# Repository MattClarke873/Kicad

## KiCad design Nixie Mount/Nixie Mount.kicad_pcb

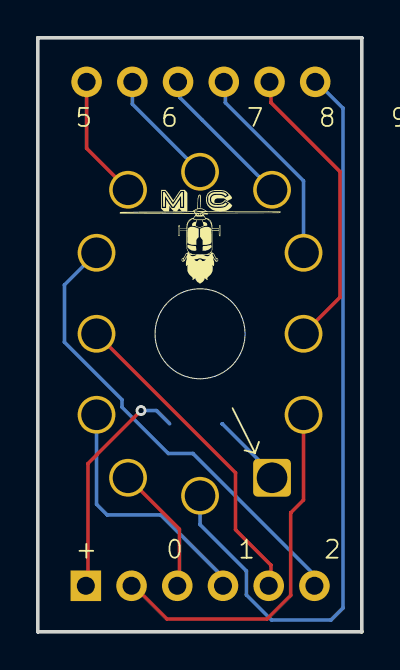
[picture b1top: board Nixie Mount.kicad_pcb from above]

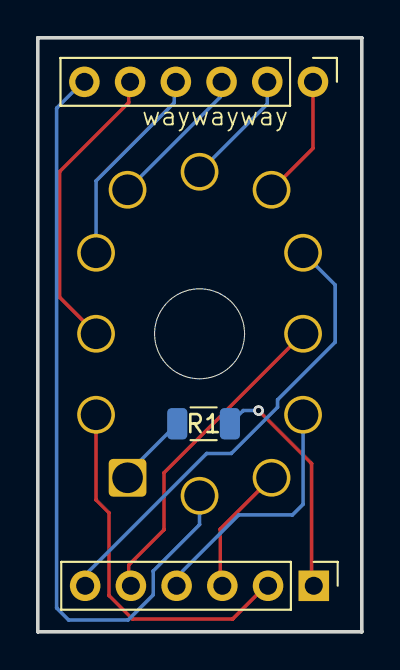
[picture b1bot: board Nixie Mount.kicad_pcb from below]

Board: 2 copper layers, 18.0 x 33.0 mm, 4 parts (3 on the bottom side), 13 nets.

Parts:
J1, J2: TSW-106-07-G-S-LL; PinHeader_1x06_P2.54mm_Vertical
NT1: IN-12
R1: R; R_1206_3216Metric

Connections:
unnamed: J2.1, NT1.7
unnamed: J1.6, NT1.8
unnamed: J1.5, NT1.9
unnamed: J1.4, NT1.10
unnamed: J1.3, NT1.11
unnamed: J2.6, NT1.12
unnamed: J1.1, R1.1
unnamed: J1.2, NT1.2
unnamed: J2.5, NT1.3
unnamed: J2.4, NT1.4
unnamed: J2.3, NT1.5
unnamed: J2.2, NT1.6
unnamed: NT1.1, R1.2

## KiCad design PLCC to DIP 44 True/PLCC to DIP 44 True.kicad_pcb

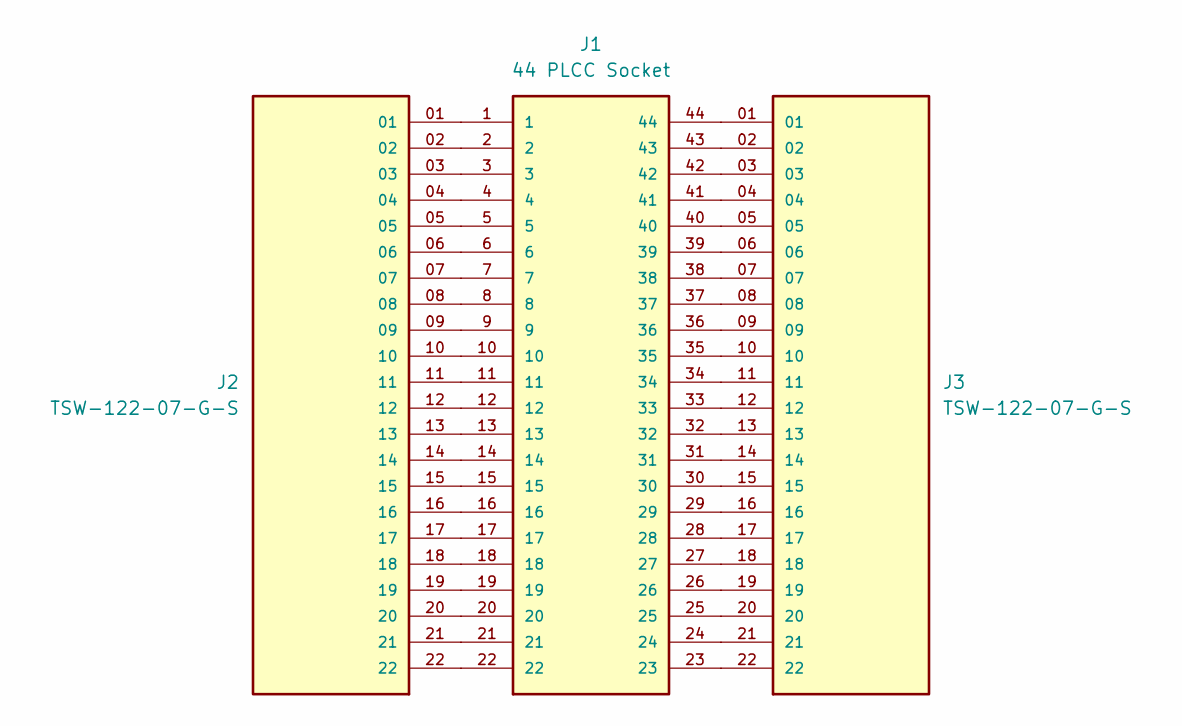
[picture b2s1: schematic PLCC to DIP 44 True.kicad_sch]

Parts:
J1: 44 PLCC Socket; AMPHENOL_54020-44030LF; PARTREV K
J2, J3: TSW-122-07-G-S; SAMTEC_TSW-122-07-G-S; PARTREV R

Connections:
unnamed: J1.1, J2.01
unnamed: J1.2, J2.02
unnamed: J1.3, J2.03
unnamed: J1.4, J2.04
unnamed: J1.5, J2.05
unnamed: J1.6, J2.06
unnamed: J1.7, J2.07
unnamed: J1.8, J2.08
unnamed: J1.9, J2.09
unnamed: J1.10, J2.10
unnamed: J1.11, J2.11
unnamed: J1.12, J2.12
unnamed: J1.13, J2.13
unnamed: J1.14, J2.14
unnamed: J1.15, J2.15
unnamed: J1.16, J2.16
unnamed: J1.17, J2.17
unnamed: J1.18, J2.18
unnamed: J1.19, J2.19
unnamed: J1.20, J2.20
unnamed: J1.21, J2.21
unnamed: J1.22, J2.22
unnamed: J1.23, J3.22
unnamed: J1.24, J3.21
unnamed: J1.25, J3.20
unnamed: J1.26, J3.19
unnamed: J1.27, J3.18
unnamed: J1.28, J3.17
unnamed: J1.29, J3.16
unnamed: J1.30, J3.15
unnamed: J1.31, J3.14
unnamed: J1.32, J3.13
unnamed: J1.33, J3.12
unnamed: J1.34, J3.11
unnamed: J1.35, J3.10
unnamed: J1.36, J3.09
unnamed: J1.37, J3.08
unnamed: J1.38, J3.07
unnamed: J1.39, J3.06
unnamed: J1.40, J3.05
unnamed: J1.41, J3.04
unnamed: J1.42, J3.03
unnamed: J1.43, J3.02
unnamed: J1.44, J3.01

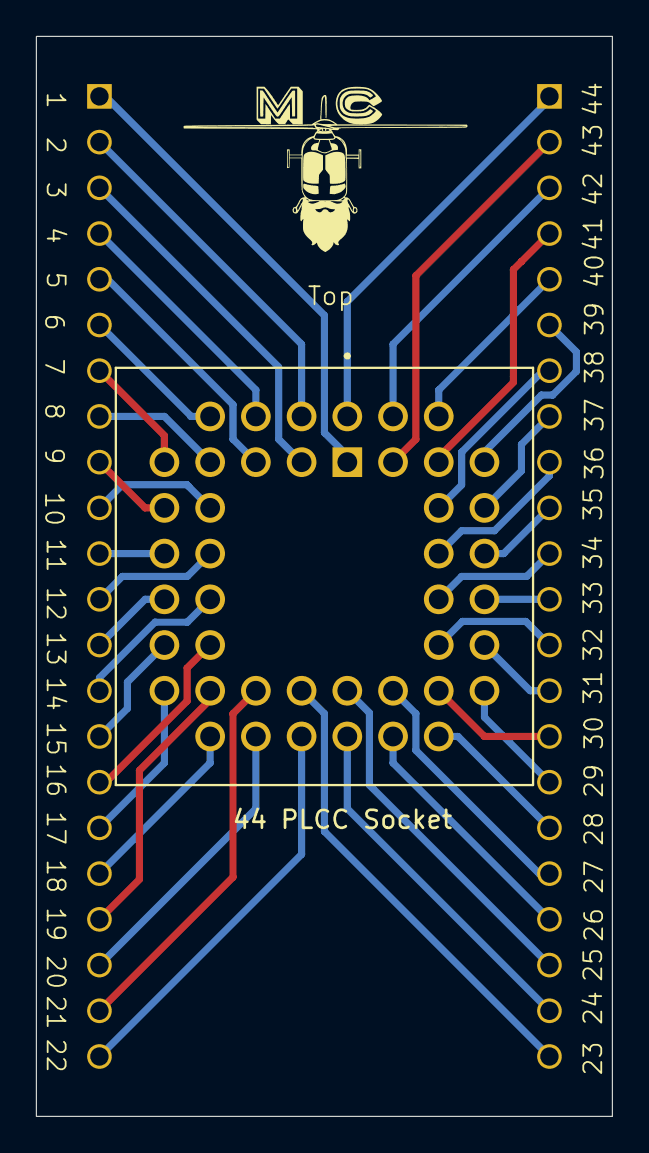
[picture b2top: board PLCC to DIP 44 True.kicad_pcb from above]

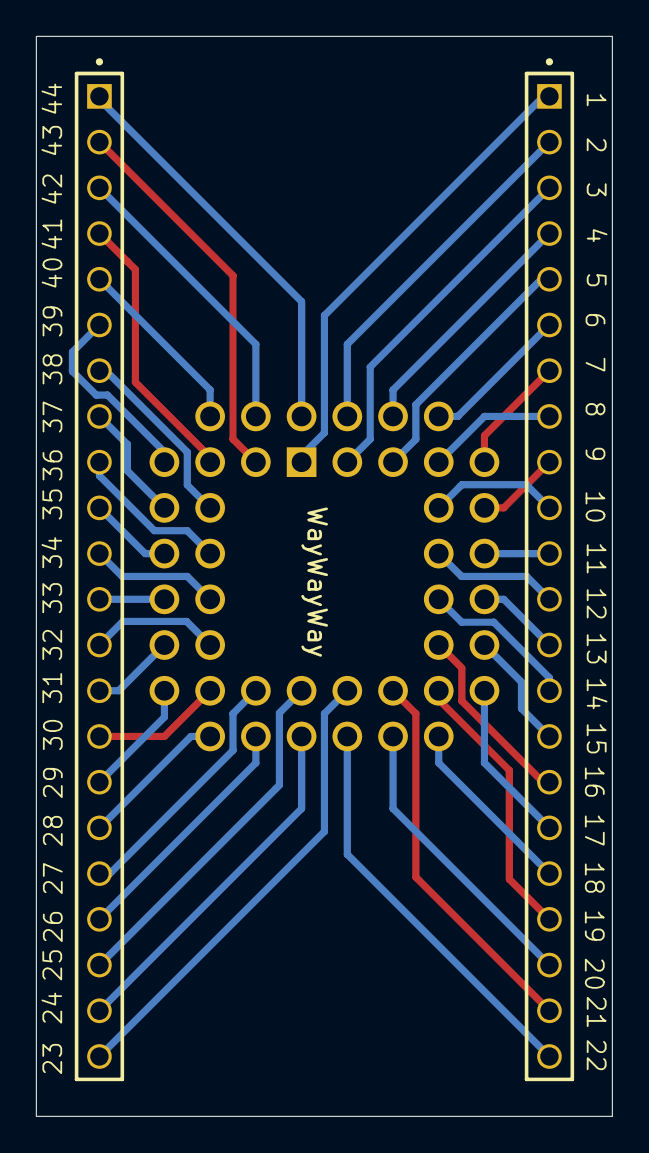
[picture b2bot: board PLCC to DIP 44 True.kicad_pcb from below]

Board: 2 copper layers, 32.0 x 60.0 mm, 3 parts (2 on the bottom side), 44 nets.

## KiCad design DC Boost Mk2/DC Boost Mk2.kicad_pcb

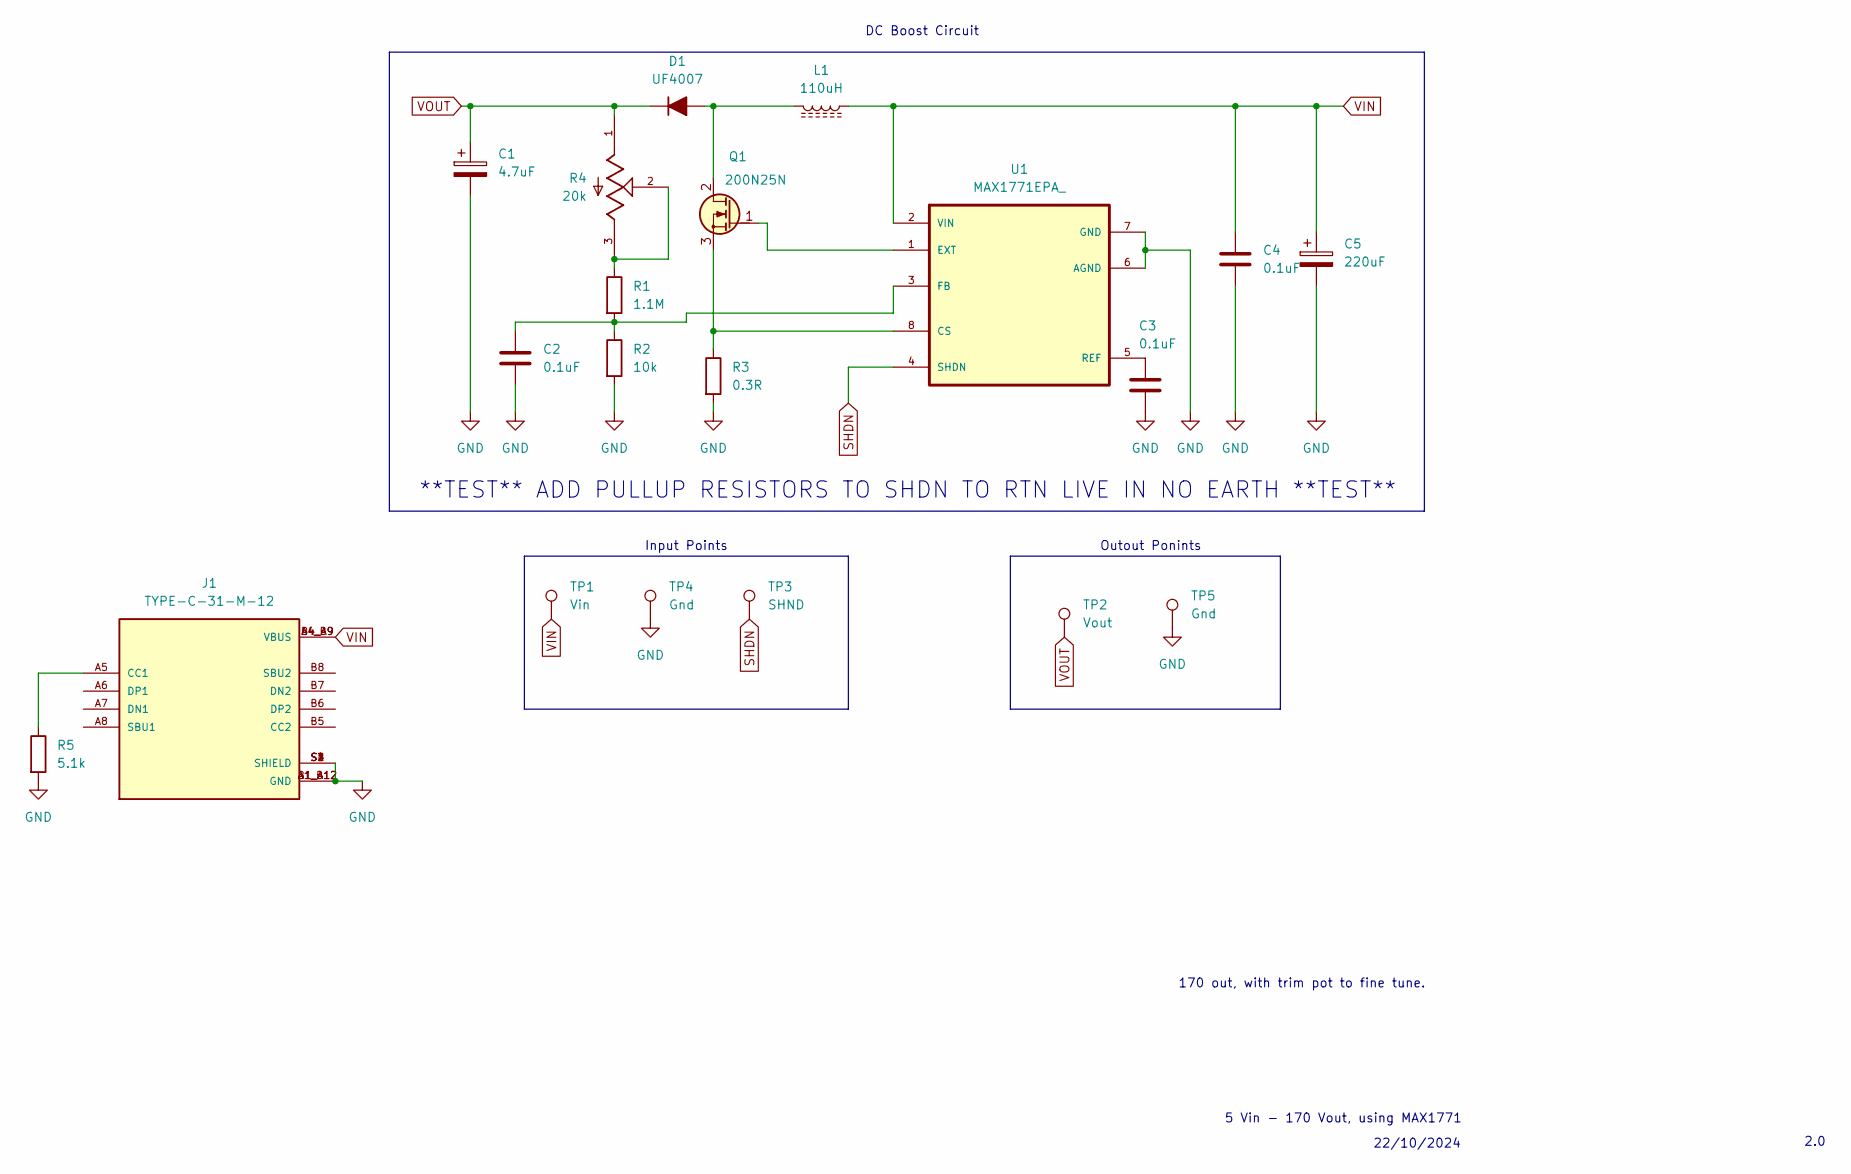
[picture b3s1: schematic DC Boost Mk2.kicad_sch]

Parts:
C1: 4.7uF; CP_Radial_D6.3mm_P2.50mm
C2, C3, C4: 0.1uF; C_1206_3216Metric_Pad1.42x1.75mm_HandSolder
C5: 220uF; CP_Radial_D6.3mm_P2.50mm
D1: UF4007; D_DO-41_SOD81_P10.16mm_Horizontal
J1: TYPE-C-31-M-12; HRO_TYPE-C-31-M-12; PARTREV 2020.12.08
L1: 110uH; L_Wuerth_HCI-1335
Q1: 200N25N; TO-220-3_Vertical_GDS
R1: 1.1M; R_1206_3216Metric_Pad1.30x1.75mm_HandSolder
R2: 10k; R_1206_3216Metric_Pad1.30x1.75mm_HandSolder
R3: 0.3R; R_1206_3216Metric_Pad1.30x1.75mm_HandSolder
R4: 20k; TRIM_TC33X-2-302E
R5: 5.1k; R_1206_3216Metric_Pad1.30x1.75mm_HandSolder
TP1: Vin; PinHeader_1x01_P1.00mm_Vertical
TP2: Vout; PinHeader_1x01_P1.00mm_Vertical
TP3: SHND; PinHeader_1x01_P1.00mm_Vertical
TP4, TP5: Gnd; PinHeader_1x01_P1.00mm_Vertical
U1: MAX1771EPA_; DIP794W47P254L991H457Q8

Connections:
GND: C1.2, C2.2, C3.2, C4.2, C5.2, J1.A1_B12 (GND), J1.B1_A12 (GND), J1.S1 (SHIELD), J1.S2 (SHIELD), J1.S3 (SHIELD), J1.S4 (SHIELD), R2.2, R3.2, R5.2, TP4.1, TP5.1, U1.6 (AGND), U1.7 (GND)
unnamed: D1.2 (A), L1.2, Q1.2 (D)
unnamed: J1.A5 (CC1), R5.1
unnamed: Q1.1 (G), U1.1 (EXT)
unnamed: Q1.3 (S), R3.1, U1.8 (CS)
unnamed: R1.1, R4.2, R4.3
unnamed: C2.1, R1.2, R2.1, U1.3 (FB)
unnamed: C3.1, U1.5 (REF)
SHDN: TP3.1, U1.4 (SHDN)
VIN: C4.1, C5.1, J1.A4_B9 (VBUS), J1.B4_A9 (VBUS), L1.1, TP1.1, U1.2 (VIN)
VOUT: C1.1, D1.1 (K), R4.1, TP2.1

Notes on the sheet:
170 out, with trim pot to fine tune.
2.0
Input Points
DC Boost Circuit
Outout Ponints
5 Vin - 170 Vout, using MAX1771
22/10/2024
**TEST** ADD PULLUP RESISTORS TO SHDN TO RTN LIVE IN NO EARTH **TEST**

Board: 2 copper layers, 20 parts (0 on the bottom side), 11 nets, no tracks yet.
